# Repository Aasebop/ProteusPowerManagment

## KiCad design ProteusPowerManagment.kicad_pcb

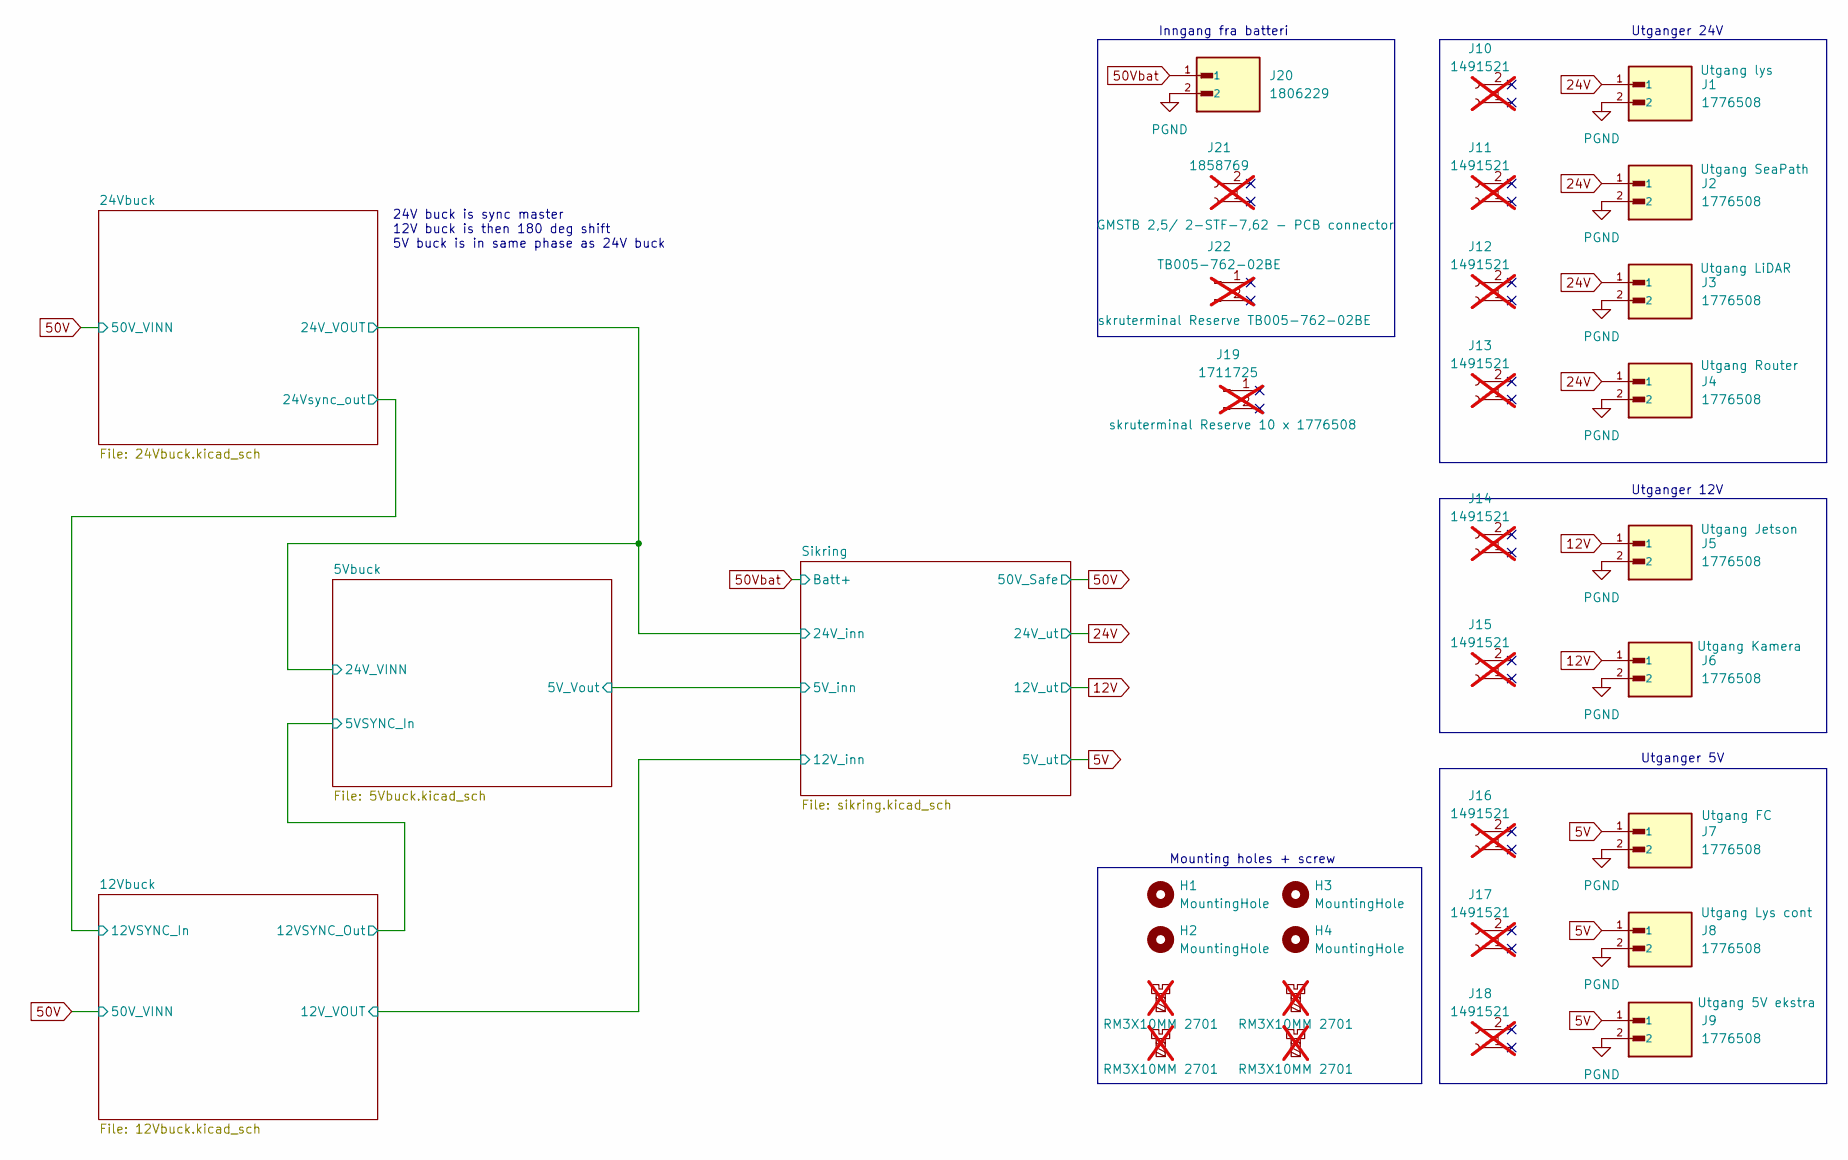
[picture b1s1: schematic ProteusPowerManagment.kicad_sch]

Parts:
H1, H2, H3, H4: MountingHole; MountingHole_3.2mm_M3
H5, H6, H7, H8: M3MountingScrew; not fitted
J1, J2, J3, J4, J5, J6, J7, J8, J9: 1776508; PHOENIX_1776508; PARTREV 06.02.2024
J10, J11, J12, J13, J14, J15, J16, J17, J18: 1491521; not fitted
J19: 1711725; not fitted
J20: 1806229; PHOENIX_1806229; PARTREV 27.10.2021
J21: 1858769; not fitted
J22: TB005-762-02BE; not fitted

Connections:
5V: J7.1, J8.1, J9.1; also elsewhere on the board
12V: J5.1, J6.1; also elsewhere on the board
24V: J1.1, J2.1, J3.1, J4.1; also elsewhere on the board
50Vbat: J20.1; also elsewhere on the board
PGND: J1.2, J2.2, J3.2, J4.2, J5.2, J6.2, J7.2, J8.2, J9.2, J20.2; also elsewhere on the board

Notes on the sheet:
Mounting holes + screw
24V buck is sync master 12V buck is then 180 deg shift 5V buck is in same phase as 24V buck
Utganger 12V
Utganger 5V
Utganger 24V
Inngang fra batteri

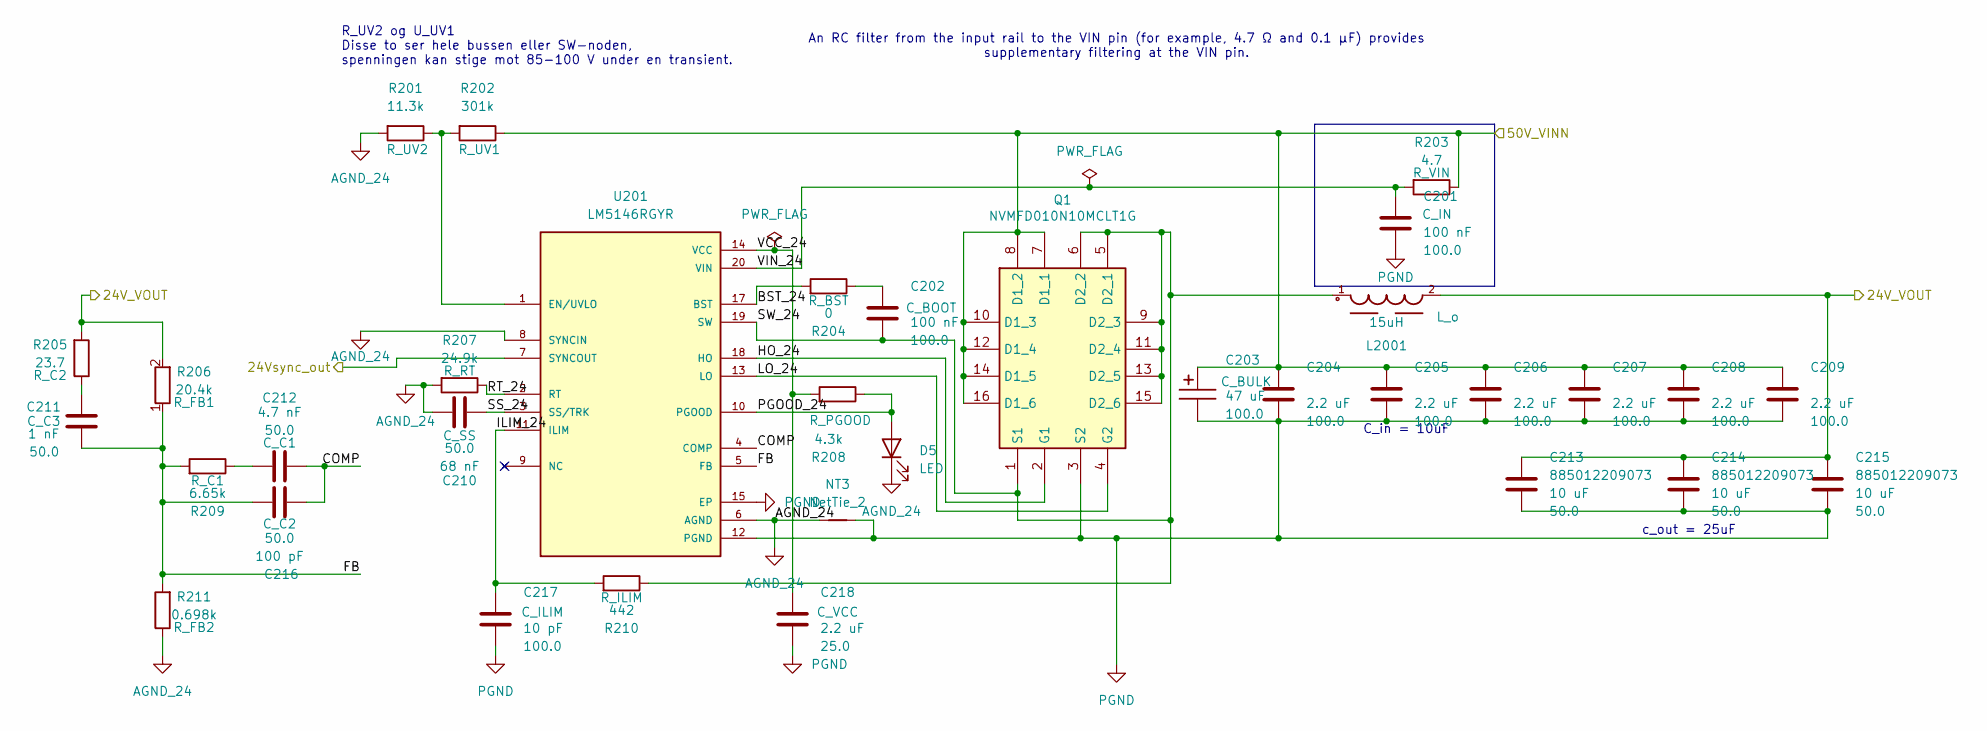
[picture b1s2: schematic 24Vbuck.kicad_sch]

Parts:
C201, C202: 100 nF; C_Wurth_WCAP-CSGP-0603_R; Voltage 100.0; Part Number 885012206120
C203: 47 uF; CP_Wurth_WCAP-ASLI-D12.5L14; Voltage 100.0; Part Number 865080862008
C204, C205, C206, C207, C208, C209: 2.2 uF; C_Wurth_WCAP-CSGP-1210_H2.5; Voltage 100.0; Part Number 885012209071
C210: 68 nF; C_Wurth_WCAP-CSGP-0603_R; Voltage 50.0; Part Number 885012206094
C211: 1 nF; C_0603_1608Metric_Pad1.08x0.95mm_HandSolder; Voltage 50.0; Part Number 885012006063
C212: 4.7 nF; C_Wurth_WCAP-CSGP-0805_H1.25_R; Voltage 50.0; Part Number 885012007067
C213, C214, C215: 10 uF; C_Wurth_WCAP-CSGP-1210_H2.5; Voltage 50.0; Part Number 885012209073
C216: 100 pF; C_Wurth_WCAP-CSGP-0603_R; Voltage 50.0; Part Number 885012006057
C217: 10 pF; C_Wurth_WCAP-CSGP-0603_R; Voltage 100.0; Part Number 885012006073
C218: 2.2 uF; C_Wurth_WCAP-CSGP-0805_H0.8_R; Voltage 25.0; Part Number 885012207079
D5: LED; LED_0603_1608Metric_Pad1.05x0.95mm_HandSolder
L2001: 15uH; WE-XHMI_1510
NT3: NetTie_2; NetTie
Q1: NVMFD010N10MCLT1G; NVMFD5C674NLT1G; Manufacturer_Part_Number NVMFD010N10MCLT1G
R201: 11.3k; R_0603_1608Metric_Pad0.98x0.95mm_HandSolder
R202: 301k; R_0805_2012Metric
R203: 4.7; R_0603_1608Metric_Pad0.98x0.95mm_HandSolder
R204: 0; R_0603_1608Metric_Pad0.98x0.95mm_HandSolder
R205: 23.7; R_0603_1608Metric_Pad0.98x0.95mm_HandSolder
R206: 20.4k; R_0603_1608Metric_Pad0.98x0.95mm_HandSolder
R207: 24.9k; R_0603_1608Metric_Pad0.98x0.95mm_HandSolder
R208: 4.3k; R_0603_1608Metric_Pad0.98x0.95mm_HandSolder
R209: 6.65k; R_0603_1608Metric_Pad0.98x0.95mm_HandSolder
R210: 442; R_0805_2012Metric_Pad1.20x1.40mm_HandSolder
R211: 0.698k; R_0603_1608Metric_Pad0.98x0.95mm_HandSolder
U201: LM5146RGYR; IC_LM5146RGYR; PARTREV A

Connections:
50Vbat: C203.1, C204.1, C205.1, C206.1, C207.1, C208.1, C209.1, Q1.7 (D1_1), Q1.8 (D1_2), Q1.10 (D1_3), Q1.12 (D1_4), Q1.14 (D1_5), Q1.16 (D1_6), R202.1, R203.1; also elsewhere on the board
/12Vbuck/12VSYNC_In: U201.7 (SYNCOUT); also elsewhere on the board
/24Vbuck/24V_VOUT: C213.1, C214.1, C215.1, L2001.2, R205.2, R206.2; also elsewhere on the board
/24Vbuck/BST_24: R204.2, U201.17 (BST)
/24Vbuck/COMP: C212.2, C216.1, U201.4 (COMP)
/24Vbuck/FB: C211.2, C216.2, R206.1, R209.2, R211.2, U201.5 (FB)
/24Vbuck/HO_24: Q1.2 (G1), U201.18 (HO)
/24Vbuck/ILIM_24: C217.1, R210.2, U201.11 (ILIM)
/24Vbuck/LO_24: Q1.4 (G2), U201.13 (LO)
/24Vbuck/PGOOD_24: D5.2 (A), R208.1, U201.10 (PGOOD)
/24Vbuck/RT_24: R207.1, U201.2 (RT)
/24Vbuck/SS_24: C210.2, U201.3 (SS/TRK)
/24Vbuck/SW_24: C202.2, L2001.1, Q1.1 (S1), Q1.5 (D2_1), Q1.6 (D2_2), Q1.9 (D2_3), Q1.11 (D2_4), Q1.13 (D2_5), Q1.15 (D2_6), R210.1, U201.19 (SW)
/24Vbuck/VCC_24: C218.1, R208.2, U201.14 (VCC)
/24Vbuck/VIN_24: C201.1, R203.2, U201.20 (VIN)
AGND_24: C210.1, D5.1 (K), NT3.2, R201.2, R207.2, R211.1, U201.6 (AGND), U201.8 (SYNCIN)
unnamed: C202.1, R204.1
unnamed: C211.1, R205.1
unnamed: C212.1, R209.1
unnamed: R201.1, R202.2, U201.1 (EN/UVLO)
PGND: C201.2, C203.2, C204.2, C205.2, C206.2, C207.2, C208.2, C209.2, C213.2, C214.2, C215.2, C217.2, C218.2, NT3.1, Q1.3 (S2), U201.12 (PGND), U201.15 (EP), U201.21 (EP); also elsewhere on the board

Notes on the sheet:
C_in = 10uF
c_out = 25uF
R_UV2 og U_UV1 Disse to ser hele bussen eller SW-noden, spenningen kan stige mot 85-100 V under en transient.
An RC filter from the input rail to the VIN pin (for example, 4.7 Ω and 0.1 µF) provides supplementary filtering at the VIN pin.

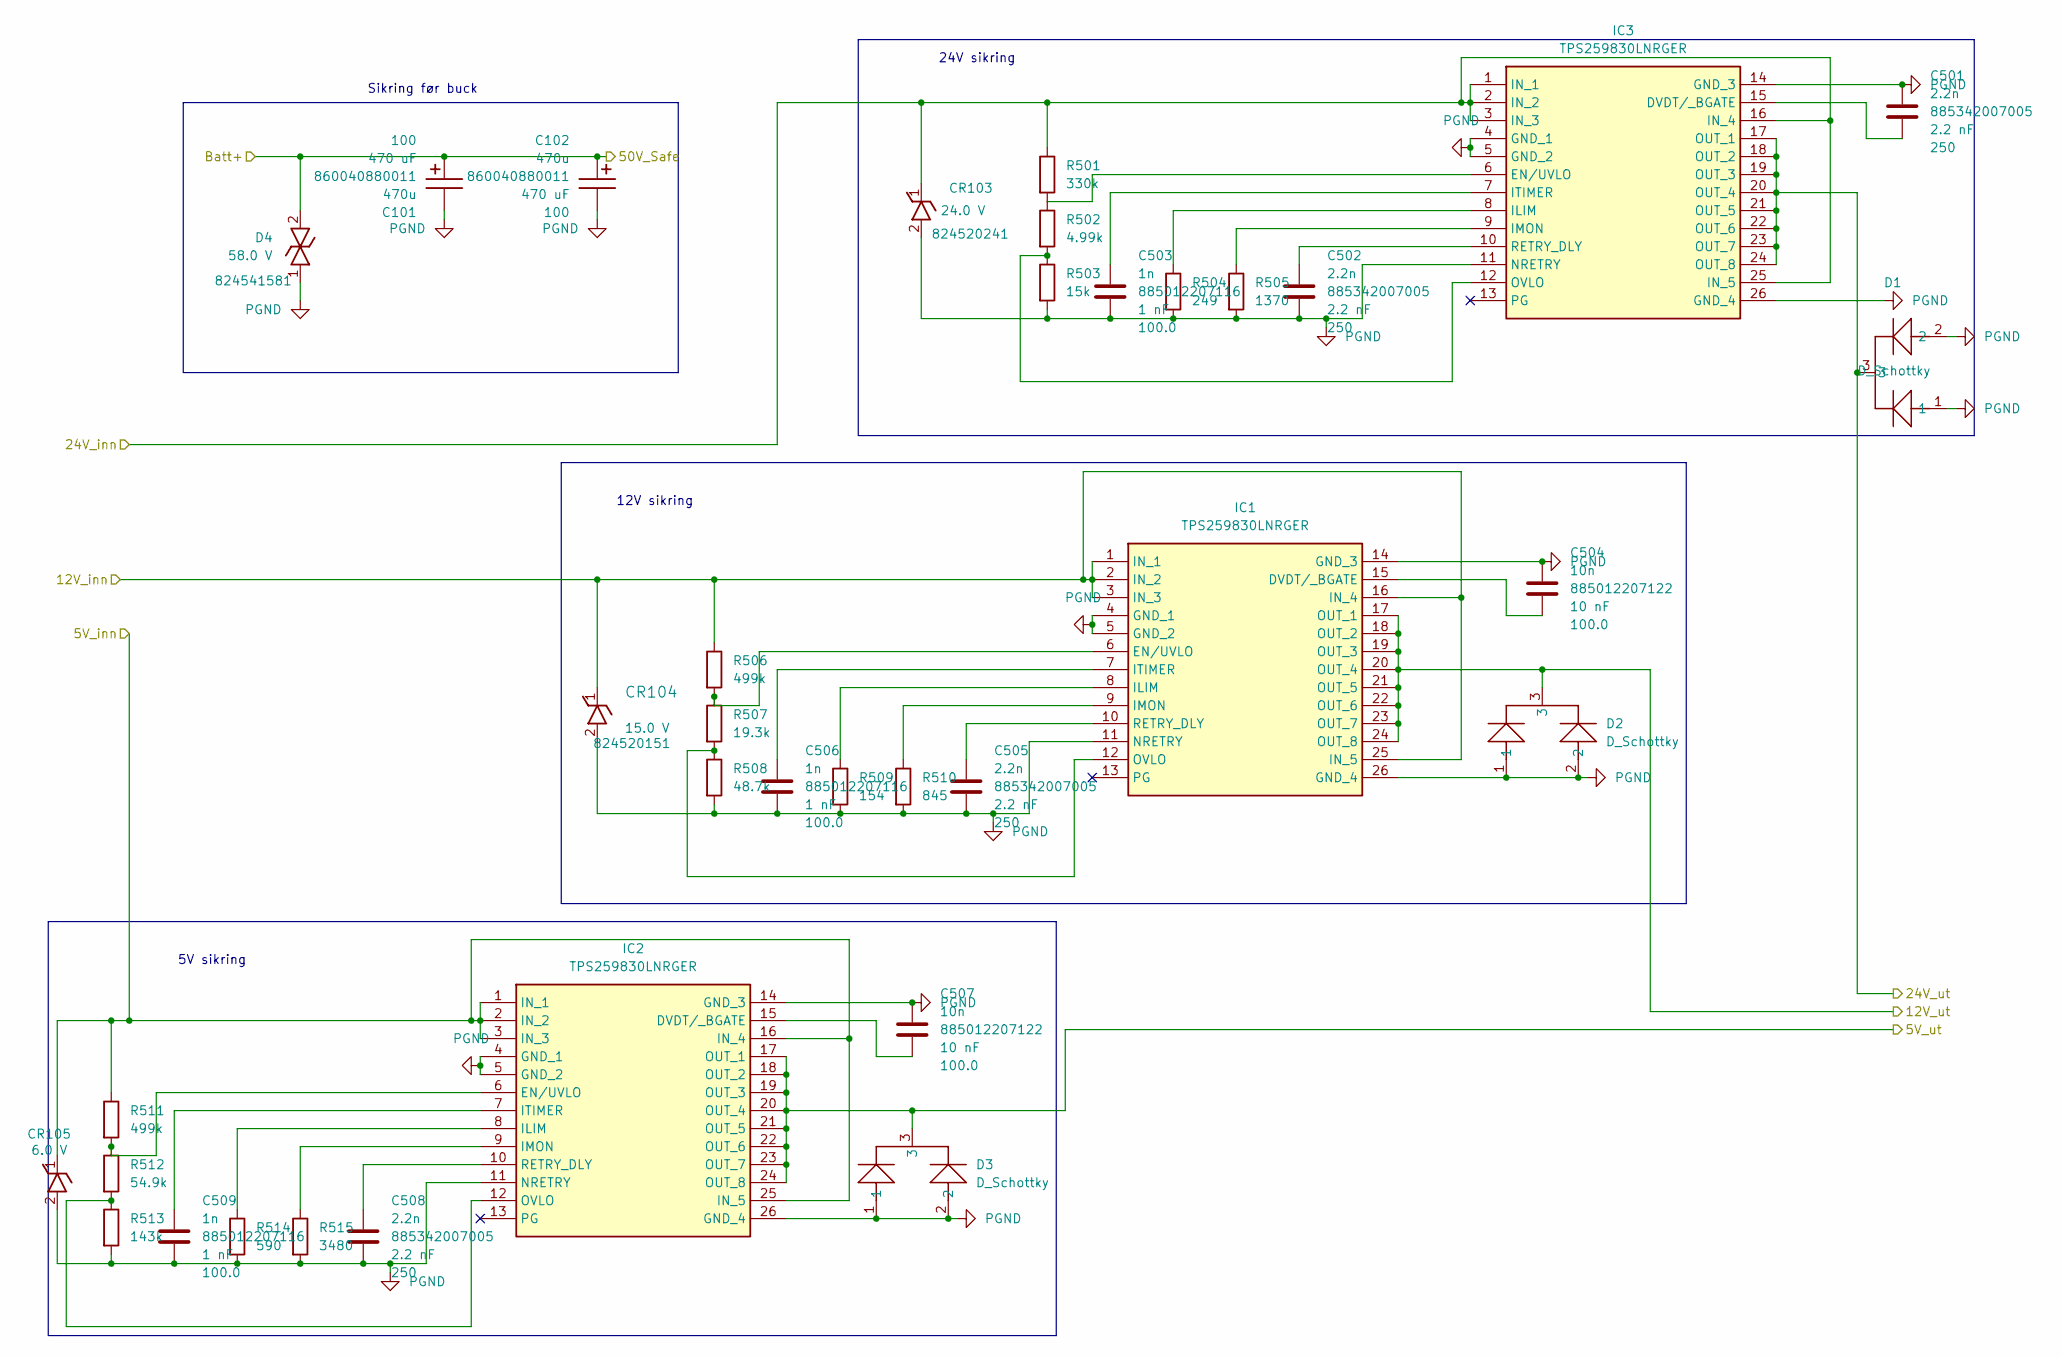
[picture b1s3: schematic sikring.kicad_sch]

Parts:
C101, C102: 470u; CP_Wurth_WCAP-ATUL-P7.5D16L35.5; Voltage 100; Part Number 860040880011
C501, C502, C505, C508: 2.2n; C_Wurth_WCAP-CSMH-0805_H1.25_R; Voltage 250; Part Number 885342007005
C503, C506, C509: 1n; C_Wurth_WCAP-CSGP-0805_H0.8_R; Voltage 100.0; Part Number 885012207116
C504, C507: 10n; C_Wurth_WCAP-CSGP-0805_H0.8_R; Voltage 100.0; Part Number 885012207122
CR103: D_Wurth_WE-TVSP-DO214-AA-600W_UNI; Part Number 824520241
CR104: D_Wurth_WE-TVSP-DO214-AA-600W_UNI; Part Number 824520151
CR105: D_Wurth_WE-TVSP-DO214-AC-400W_UNI; Part Number 824500600
D1, D2, D3: D_Schottky; DIODE_TO-277A
D4: DO214-AB-1500W_BI_824541581; D_Wurth_WE-TVSP-DO214-AB-1500W_BI; Part Number 824541581
IC1, IC2, IC3: TPS259830LNRGER; Mouser Part Number 595-TPS259830LNRGER
R501: 330k; R_0603_1608Metric_Pad0.98x0.95mm_HandSolder
R502: 4.99k; R_0603_1608Metric_Pad0.98x0.95mm_HandSolder
R503: 15k; R_0603_1608Metric_Pad0.98x0.95mm_HandSolder
R504: 249; R_0805_2012Metric_Pad1.20x1.40mm_HandSolder
R505: 1370; R_0805_2012Metric_Pad1.20x1.40mm_HandSolder
R506, R511: 499k; R_0805_2012Metric_Pad1.20x1.40mm_HandSolder
R507: 19.3k; R_0805_2012Metric_Pad1.20x1.40mm_HandSolder
R508: 48.7k; R_0805_2012Metric_Pad1.20x1.40mm_HandSolder
R509: 154; R_0805_2012Metric_Pad1.20x1.40mm_HandSolder
R510: 845; R_0805_2012Metric_Pad1.20x1.40mm_HandSolder
R512: 54.9k; R_0805_2012Metric_Pad1.20x1.40mm_HandSolder
R513: 143k; R_0805_2012Metric_Pad1.20x1.40mm_HandSolder
R514: 590; R_0805_2012Metric_Pad1.20x1.40mm_HandSolder
R515: 3480; R_0805_2012Metric_Pad1.20x1.40mm_HandSolder

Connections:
5V: D3.3, IC2.17 (OUT_1), IC2.18 (OUT_2), IC2.19 (OUT_3), IC2.20 (OUT_4), IC2.21 (OUT_5), IC2.22 (OUT_6), IC2.23 (OUT_7), IC2.24 (OUT_8); also elsewhere on the board
12V: D2.3, IC1.17 (OUT_1), IC1.18 (OUT_2), IC1.19 (OUT_3), IC1.20 (OUT_4), IC1.21 (OUT_5), IC1.22 (OUT_6), IC1.23 (OUT_7), IC1.24 (OUT_8); also elsewhere on the board
24V: D1.3, IC3.17 (OUT_1), IC3.18 (OUT_2), IC3.19 (OUT_3), IC3.20 (OUT_4), IC3.21 (OUT_5), IC3.22 (OUT_6), IC3.23 (OUT_7), IC3.24 (OUT_8); also elsewhere on the board
50Vbat: C101.1, C102.1, D4.2; also elsewhere on the board
/5Vbuck/5V_Vout: CR105.1 (Cathode), IC2.1 (IN_1), IC2.2 (IN_2), IC2.3 (IN_3), IC2.16 (IN_4), IC2.25 (IN_5), R511.1; also elsewhere on the board
/12Vbuck/12V_VOUT: CR104.1 (Cathode), IC1.1 (IN_1), IC1.2 (IN_2), IC1.3 (IN_3), IC1.16 (IN_4), IC1.25 (IN_5), R506.1; also elsewhere on the board
/24Vbuck/24V_VOUT: CR103.1 (Cathode), IC3.1 (IN_1), IC3.2 (IN_2), IC3.3 (IN_3), IC3.16 (IN_4), IC3.25 (IN_5), R501.1; also elsewhere on the board
unnamed: C504.2, IC1.15 (DVDT/_BGATE)
unnamed: IC1.6 (EN/UVLO), R506.2, R507.1
unnamed: IC1.8 (ILIM), R509.1
unnamed: IC1.9 (IMON), R510.1
unnamed: C506.1, IC1.7 (ITIMER)
unnamed: IC1.12 (OVLO), R507.2, R508.1
unnamed: C505.1, IC1.10 (RETRY_DLY)
unnamed: C507.2, IC2.15 (DVDT/_BGATE)
unnamed: IC2.6 (EN/UVLO), R511.2, R512.1
unnamed: IC2.8 (ILIM), R514.1
unnamed: IC2.9 (IMON), R515.1
unnamed: C509.1, IC2.7 (ITIMER)
unnamed: IC2.12 (OVLO), R512.2, R513.1
unnamed: C508.1, IC2.10 (RETRY_DLY)
unnamed: C501.2, IC3.15 (DVDT/_BGATE)
unnamed: IC3.6 (EN/UVLO), R501.2, R502.1
unnamed: IC3.8 (ILIM), R504.1
unnamed: IC3.9 (IMON), R505.1
unnamed: C503.1, IC3.7 (ITIMER)
unnamed: IC3.12 (OVLO), R502.2, R503.1
unnamed: C502.1, IC3.10 (RETRY_DLY)
PGND: C101.2, C102.2, C501.1, C502.2, C503.2, C504.1, C505.2, C506.2, C507.1, C508.2, C509.2, CR103.2 (Anode), CR104.2 (Anode), CR105.2 (Anode), D1.1, D1.2, D2.1, D2.2, D3.1, D3.2, D4.1, IC1.4 (GND_1), IC1.5 (GND_2), IC1.11 (NRETRY), IC1.14 (GND_3), IC1.26 (GND_4), IC2.4 (GND_1), IC2.5 (GND_2), IC2.11 (NRETRY), IC2.14 (GND_3), IC2.26 (GND_4), IC3.4 (GND_1), IC3.5 (GND_2), IC3.11 (NRETRY), IC3.14 (GND_3), IC3.26 (GND_4), R503.2, R504.2, R505.2, R508.2, R509.2, R510.2, R513.2, R514.2, R515.2; also elsewhere on the board

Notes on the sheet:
5V sikring
12V sikring
24V sikring
Sikring før buck

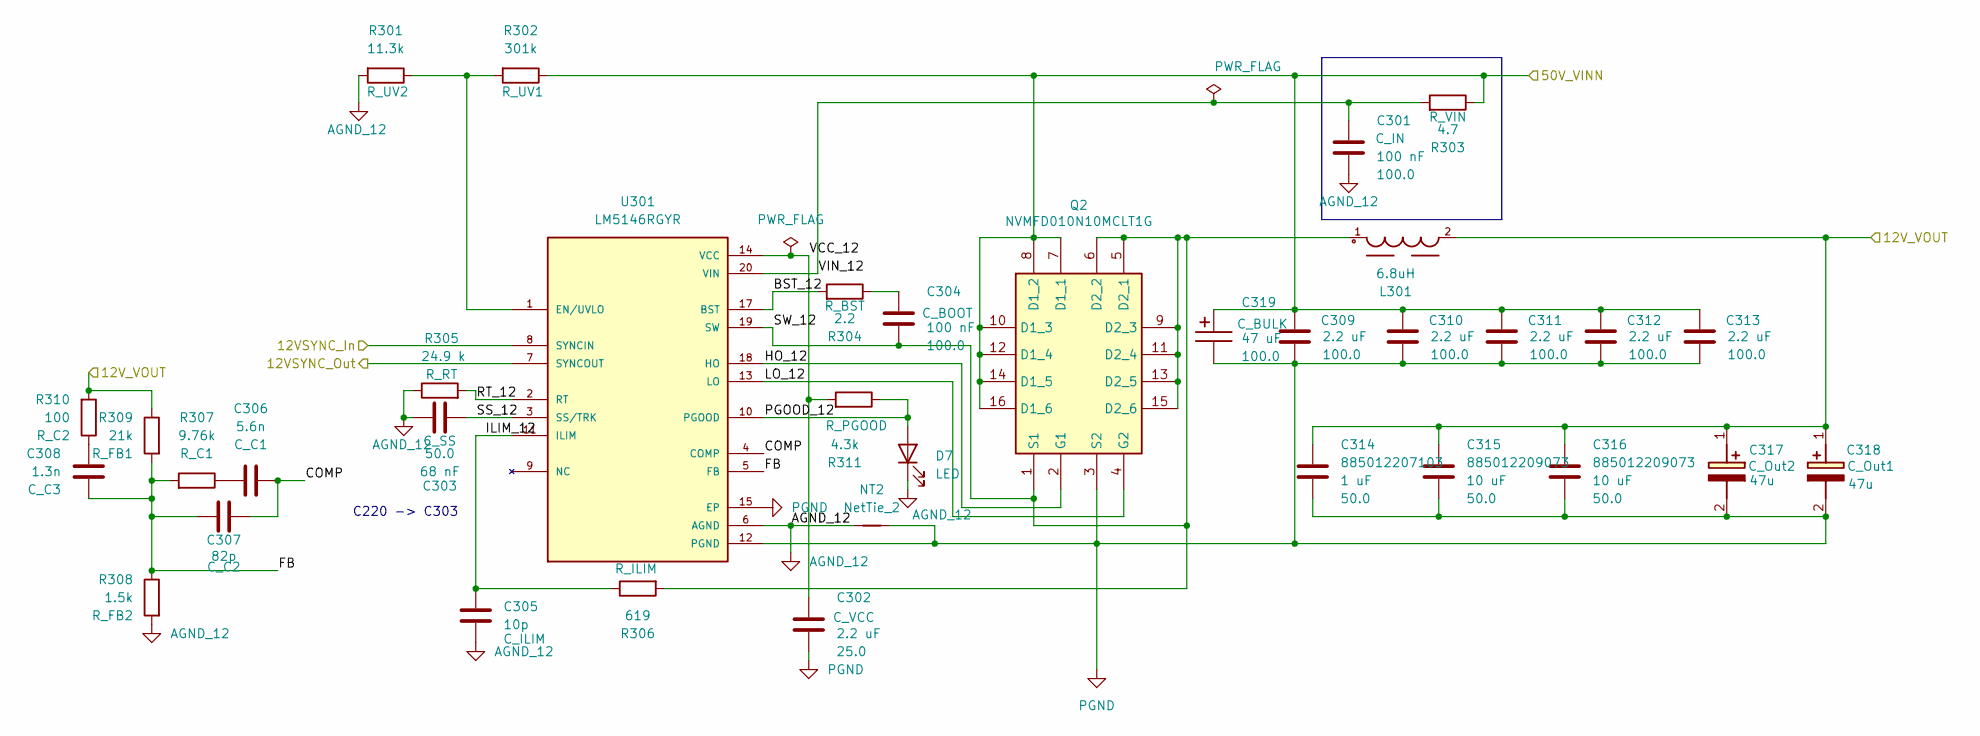
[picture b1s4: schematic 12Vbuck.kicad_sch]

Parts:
C301, C304: 100 nF; C_Wurth_WCAP-CSGP-0603_R; Voltage 100.0; Part Number 885012206120
C302: 2.2 uF; C_Wurth_WCAP-CSGP-0805_H0.8_R; Voltage 25.0; Part Number 885012207079
C303: 68 nF; C_Wurth_WCAP-CSGP-0603_R; Voltage 50.0; Part Number 885012206094
C305: 10p; C_0603_1608Metric
C306: 5.6n; C_0603_1608Metric
C307: 82p; C_0603_1608Metric
C308: 1.3n; C_0603_1608Metric
C309, C310, C311, C312, C313: 2.2 uF; C_Wurth_WCAP-CSGP-1210_H2.5; Voltage 100.0; Part Number 885012209071
C314: 1 uF; C_Wurth_WCAP-CSGP-0805_H1.25_R; Voltage 50.0; Part Number 885012207103
C315, C316: 10 uF; C_Wurth_WCAP-CSGP-1210_H2.5; Voltage 50.0; Part Number 885012209073
C317, C318: 47u; CAPAE830X1000N; Mouser Part Number 581-APA0809470M050R
C319: 47 uF; CP_Wurth_WCAP-ASLI-D12.5L14; Voltage 100.0; Part Number 865080862008
D7: LED; LED_0603_1608Metric_Pad1.05x0.95mm_HandSolder
L301: 6.8uH; L_Wurth_WE-XHMA-1510-6.8uH
NT2: NetTie_2; NetTie
Q2: NVMFD010N10MCLT1G; NVMFD5C674NLT1G; Mouser Part Number NVMFD010N10MCLT1G
R301: 11.3k; R_0603_1608Metric_Pad0.98x0.95mm_HandSolder
R302: 301k; R_0805_2012Metric
R303: 4.7; R_0603_1608Metric_Pad0.98x0.95mm_HandSolder
R304: 2.2; R_0603_1608Metric_Pad0.98x0.95mm_HandSolder
R305: 24.9 k; R_0603_1608Metric
R306: 619; R_0603_1608Metric
R307: 9.76k; R_0603_1608Metric
R308: 1.5k; R_0603_1608Metric
R309: 21k; R_0603_1608Metric
R310: 100; R_0603_1608Metric
R311: 4.3k; R_0603_1608Metric_Pad0.98x0.95mm_HandSolder
U301: LM5146RGYR; IC_LM5146RGYR; PARTREV A

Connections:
50Vbat: C309.1, C310.1, C311.1, C312.1, C313.1, C319.1, Q2.7 (D1_1), Q2.8 (D1_2), Q2.10 (D1_3), Q2.12 (D1_4), Q2.14 (D1_5), Q2.16 (D1_6), R302.1, R303.1; also elsewhere on the board
/12Vbuck/12VSYNC_In: U301.8 (SYNCIN); also elsewhere on the board
/12Vbuck/12VSYNC_Out: U301.7 (SYNCOUT); also elsewhere on the board
/12Vbuck/12V_VOUT: C314.1, C315.1, C316.1, C317.1 (+), C318.1 (+), L301.2, R309.1, R310.2; also elsewhere on the board
/12Vbuck/BST_12: R304.2, U301.17 (BST)
/12Vbuck/COMP: C306.2, C307.1, U301.4 (COMP)
/12Vbuck/FB: C307.2, C308.1, R307.2, R308.1, R309.2, U301.5 (FB)
/12Vbuck/HO_12: Q2.2 (G1), U301.18 (HO)
/12Vbuck/ILIM_12: C305.1, R306.1, U301.11 (ILIM)
/12Vbuck/LO_12: Q2.4 (G2), U301.13 (LO)
/12Vbuck/PGOOD_12: D7.2 (A), R311.1, U301.10 (PGOOD)
/12Vbuck/RT_12: R305.2, U301.2 (RT)
/12Vbuck/SS_12: C303.2, U301.3 (SS/TRK)
/12Vbuck/SW_12: C304.2, L301.1, Q2.1 (S1), Q2.5 (D2_1), Q2.6 (D2_2), Q2.9 (D2_3), Q2.11 (D2_4), Q2.13 (D2_5), Q2.15 (D2_6), R306.2, U301.19 (SW)
/12Vbuck/VCC_12: C302.1, R311.2, U301.14 (VCC)
/12Vbuck/VIN_12: C301.1, R303.2, U301.20 (VIN)
AGND_12: C301.2, C303.1, C305.2, D7.1 (K), NT2.2, R301.2, R305.1, R308.2, U301.6 (AGND)
unnamed: C304.1, R304.1
unnamed: C306.1, R307.1
unnamed: C308.2, R310.1
unnamed: R301.1, R302.2, U301.1 (EN/UVLO)
PGND: C302.2, C309.2, C310.2, C311.2, C312.2, C313.2, C314.2, C315.2, C316.2, C317.2 (-), C318.2 (-), C319.2, NT2.1, Q2.3 (S2), U301.12 (PGND), U301.15 (EP), U301.21 (EP); also elsewhere on the board

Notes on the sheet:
C220 -> C303

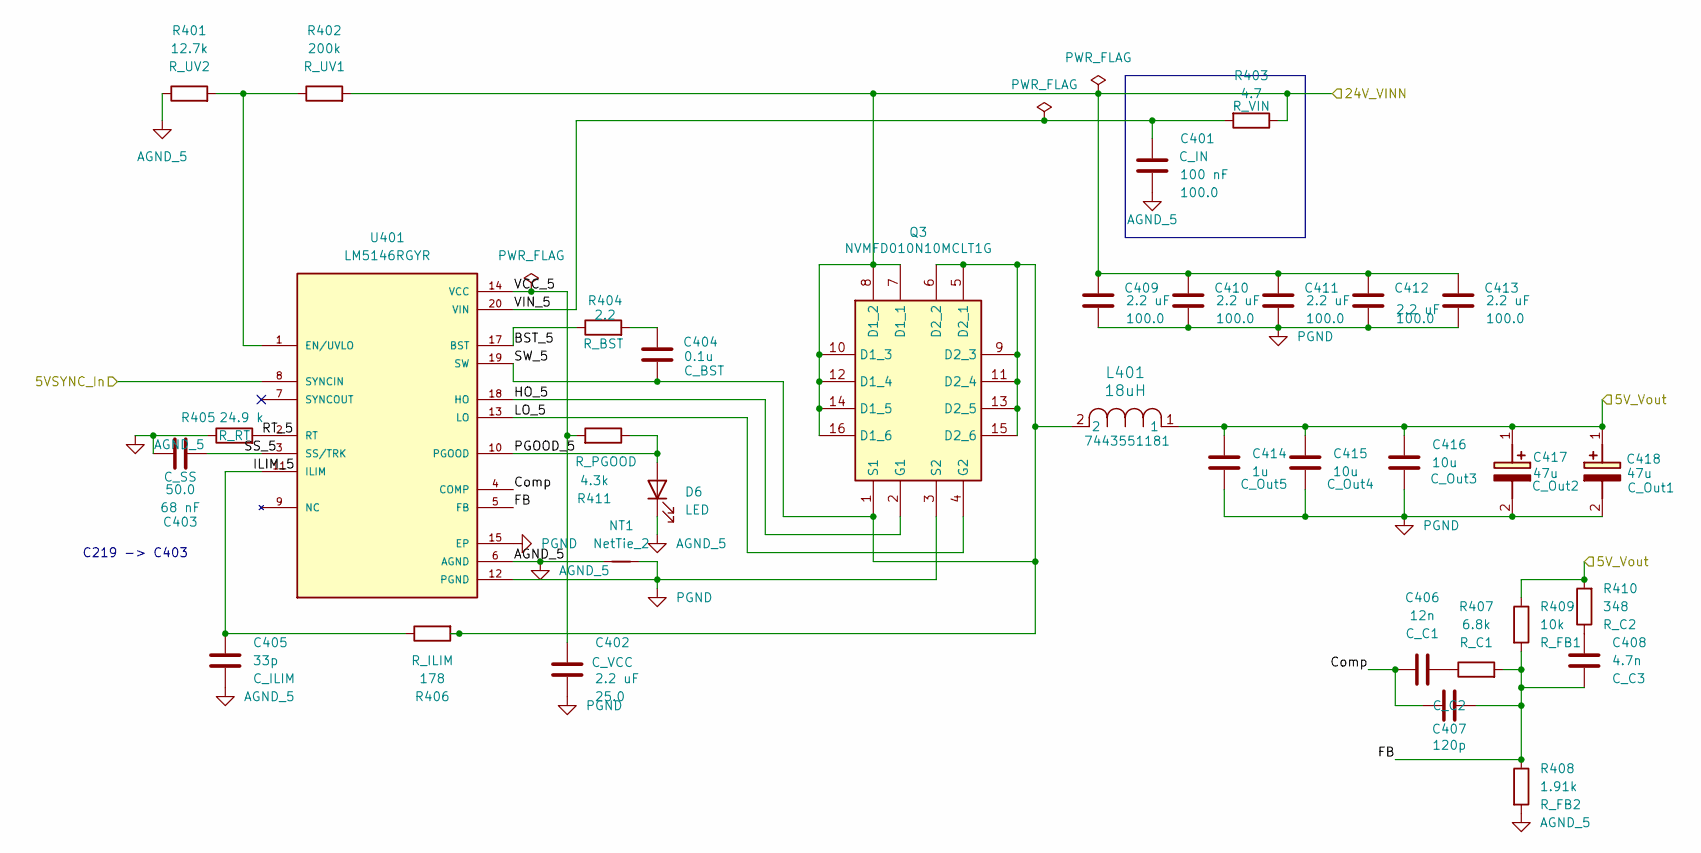
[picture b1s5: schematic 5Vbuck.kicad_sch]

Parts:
C401: 100 nF; C_Wurth_WCAP-CSGP-0603_R; Voltage 100.0; Part Number 885012206120
C402: 2.2 uF; C_Wurth_WCAP-CSGP-0805_H0.8_R; Voltage 25.0; Part Number 885012207079
C403: 68 nF; C_Wurth_WCAP-CSGP-0603_R; Voltage 50.0; Part Number 885012206094
C404: 0.1u; C_0603_1608Metric
C405: 33p; C_0603_1608Metric
C406: 12n; C_0603_1608Metric
C407: 120p; C_0603_1608Metric
C408: 4.7n; C_0603_1608Metric
C409, C410, C411, C412, C413: 2.2 uF; C_Wurth_WCAP-CSGP-1210_H2.5; Voltage 100.0; Part Number 885012209071
C414: 1u; C_0805_2012Metric
C415, C416: 10u; C_Wurth_WCAP-CSGP-1210_H2.5
C417: 47u; CAPAE830X1000N
C418: 47u; CAPAE830X1000N; Mouser Part Number 581-APA0809470M050R
D6: LED; LED_0603_1608Metric_Pad1.05x0.95mm_HandSolder
L401: 18uH; IND_1365-WE-HCI_WRE
NT1: NetTie_2; NetTie-2_SMD_Pad0.5mm
Q3: NVMFD010N10MCLT1G; NVMFD5C674NLT1G; Manufacturer_Part_Number NVMFD010N10MCLT1G
R401: 12.7k; R_0603_1608Metric
R402: 200k; R_0603_1608Metric
R403: 4.7; R_0603_1608Metric_Pad0.98x0.95mm_HandSolder
R404: 2.2; R_0603_1608Metric
R405: 24.9 k; R_0603_1608Metric
R406: 178; R_0603_1608Metric
R407: 6.8k; R_0603_1608Metric
R408: 1.91k; R_0603_1608Metric
R409: 10k; R_0603_1608Metric
R410: 348; R_0603_1608Metric
R411: 4.3k; R_0603_1608Metric_Pad0.98x0.95mm_HandSolder
U401: LM5146RGYR; IC_LM5146RGYR; PARTREV A

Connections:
/5Vbuck/5V_Vout: C414.1, C415.1, C416.1, C417.1 (+), C418.1 (+), L401.1, R409.1, R410.2; also elsewhere on the board
/5Vbuck/BST_5: R404.1, U401.17 (BST)
/5Vbuck/Comp: C406.2, C407.1, U401.4 (COMP)
/5Vbuck/FB: C407.2, C408.1, R407.2, R408.1, R409.2, U401.5 (FB)
/5Vbuck/HO_5: Q3.2 (G1), U401.18 (HO)
/5Vbuck/ILIM_5: C405.1, R406.1, U401.11 (ILIM)
/5Vbuck/LO_5: Q3.4 (G2), U401.13 (LO)
/5Vbuck/PGOOD_5: D6.2 (A), R411.1, U401.10 (PGOOD)
/5Vbuck/RT_5: R405.2, U401.2 (RT)
/5Vbuck/SS_5: C403.2, U401.3 (SS/TRK)
/5Vbuck/SW_5: C404.1, L401.2, Q3.1 (S1), Q3.5 (D2_1), Q3.6 (D2_2), Q3.9 (D2_3), Q3.11 (D2_4), Q3.13 (D2_5), Q3.15 (D2_6), R406.2, U401.19 (SW)
/5Vbuck/VCC_5: C402.1, R411.2, U401.14 (VCC)
/5Vbuck/VIN_5: C401.1, R403.2, U401.20 (VIN)
/12Vbuck/12VSYNC_Out: U401.8 (SYNCIN); also elsewhere on the board
/24Vbuck/24V_VOUT: C409.1, C410.1, C411.1, C412.1, C413.1, Q3.7 (D1_1), Q3.8 (D1_2), Q3.10 (D1_3), Q3.12 (D1_4), Q3.14 (D1_5), Q3.16 (D1_6), R402.2, R403.1; also elsewhere on the board
AGND_5: C401.2, C403.1, C405.2, D6.1 (K), NT1.2, R401.1, R405.1, R408.2, U401.6 (AGND)
unnamed: C404.2, R404.2
unnamed: C406.1, R407.1
unnamed: C408.2, R410.1
unnamed: R401.2, R402.1, U401.1 (EN/UVLO)
PGND: C402.2, C409.2, C410.2, C411.2, C412.2, C413.2, C414.2, C415.2, C416.2, C417.2 (-), C418.2 (-), NT1.1, Q3.3 (S2), U401.12 (PGND), U401.15 (EP), U401.21 (EP); also elsewhere on the board

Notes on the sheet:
C219 -> C403

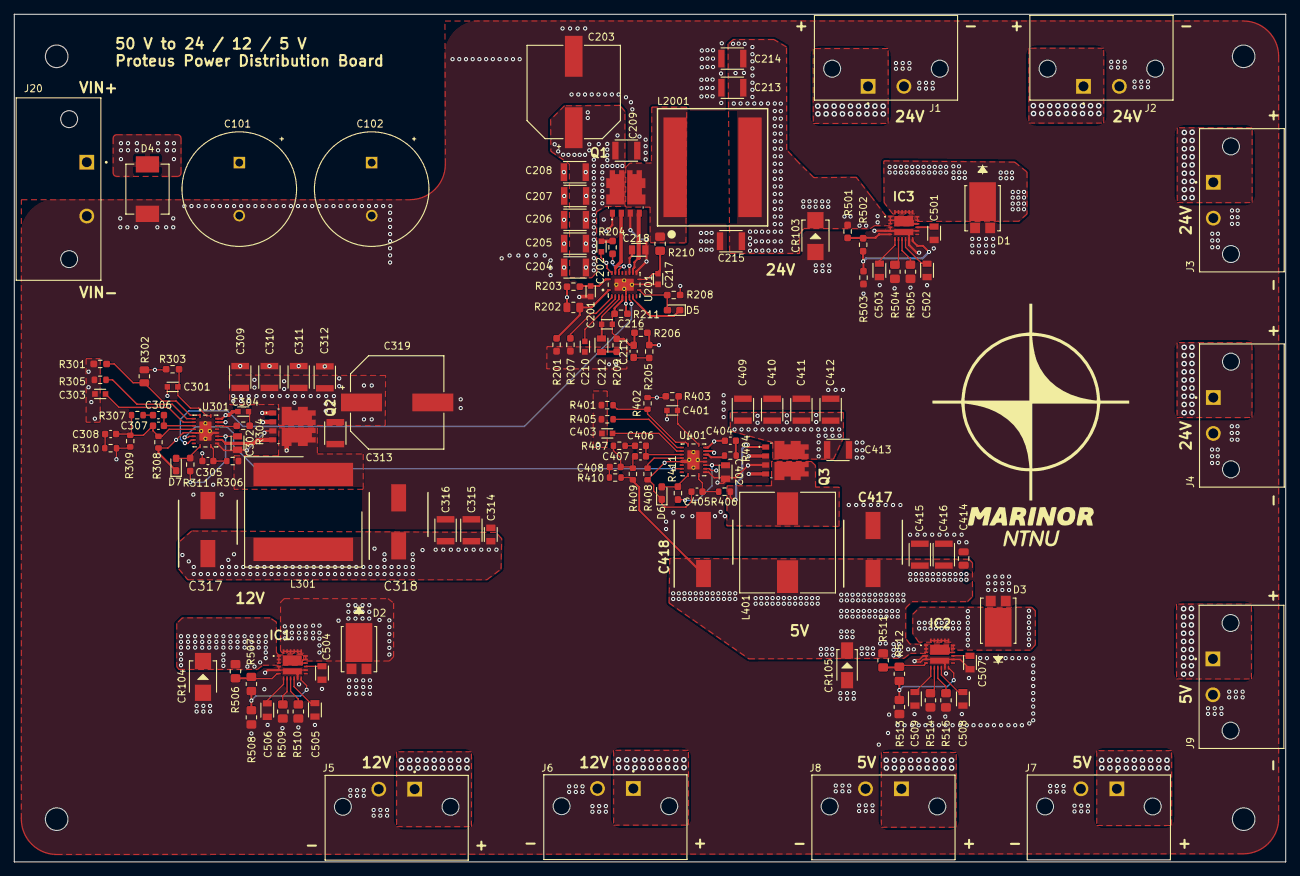
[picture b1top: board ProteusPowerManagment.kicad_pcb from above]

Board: 4 copper layers, 180.0 x 120.0 mm, 153 parts (0 on the bottom side), 82 nets.
